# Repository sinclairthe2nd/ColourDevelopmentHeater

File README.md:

# ColourDevelopmentHeater
This is a Heating Controller Designed for Develoment of Colour film by the C-41 Process.
It uses PID,PI or P to controll A 12V heating element although other voltages are possible.
Temperature is sensed by a Pt100 and is read back to the user via a 7 Segment Display.

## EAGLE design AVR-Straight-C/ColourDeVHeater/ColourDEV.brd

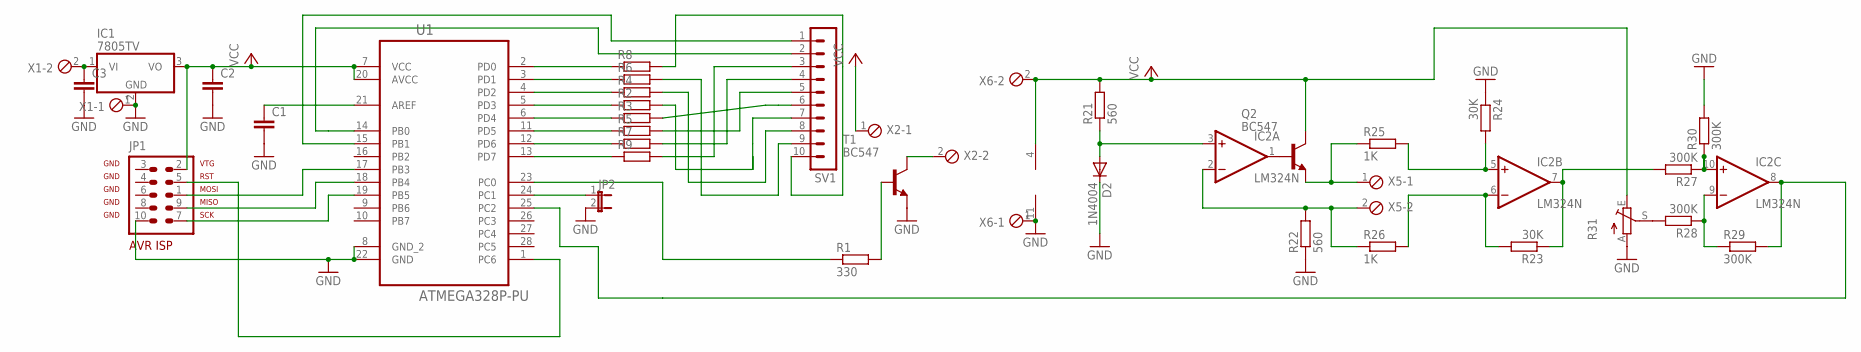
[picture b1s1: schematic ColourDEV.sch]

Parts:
C1: C-EU050-075X075; C050-075X075
C2, C3: C-EU050-025X075; C050-025X075
D2: 1N4004; DO41-10
IC1: 7805TV; TO220V
IC2: LM324N; DIL14
JP1: AVR-ISP-10
JP2: JP1E; JP1
Q2: BC547; TO92
R1: 330; M1206
R2, R3, R4, R5, R6, R7, R8, R9: R-EU_M1206; M1206
R21, R22: 560; M1206
R23, R24: 30K; M1206
R25, R26: 1K; M1206
R27, R28, R29, R30: 300K; M1206
R31: TRIM_EU-LI10; LI10
SV1: MA10-1
T1: BC547; TO92
U1: ATMEGA328P-PU; DIP254P762X457-28
X1, X2, X5, X6: MPT2; 2POL254

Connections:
GND: C1.2, C2.2, C3.2, D2.C, IC1.2 (GND), IC2.11 (V-), JP1.10, JP2.2, R22.1, R24.1, R30.2, R31.A, T1.1 (E), U1.8 (GND_2), U1.22 (GND), X1.1, X6.1
unnamed: R1.2, T1.2 (B)
unnamed: R1.1, U1.23 (PC0)
unnamed: JP1.5, U1.1 (PC6)
unnamed: JP1.1, U1.17 (PB3)
unnamed: JP1.9, U1.18 (PB4)
unnamed: JP1.7, U1.19 (PB5)
unnamed: R9.2, SV1.3
unnamed: R7.2, SV1.4
unnamed: R5.2, SV1.5
unnamed: R3.2, SV1.6
unnamed: R2.2, SV1.7
unnamed: R4.2, SV1.8
unnamed: R6.2, SV1.9
unnamed: R8.2, SV1.10
unnamed: SV1.2, U1.14 (PB0)
unnamed: SV1.1, U1.15 (PB1)
unnamed: C1.1, U1.21 (AREF)
unnamed: R5.1, U1.11 (PD5)
unnamed: R3.1, U1.6 (PD4)
unnamed: R2.1, U1.5 (PD3)
unnamed: R4.1, U1.4 (PD2)
unnamed: R6.1, U1.3 (PD1)
unnamed: R8.1, U1.2 (PD0)
unnamed: R7.1, U1.12 (PD6)
unnamed: R9.1, U1.13 (PD7)
unnamed: JP2.1, U1.24 (PC1)
unnamed: T1.3 (C), X2.2
unnamed: C3.1, IC1.1 (VI), X1.2
unnamed: D2.A, IC2.3 (+IN), R21.1
unnamed: IC2.1 (OUT), Q2.2 (B)
unnamed: Q2.1 (E), R25.1, X5.1
unnamed: IC2.2 (-IN), R22.2, R26.1, X5.2
unnamed: IC2.5 (+IN), R24.2, R25.2
unnamed: IC2.6 (-IN), R23.2, R26.2
unnamed: IC2.7 (OUT), R23.1, R27.2
unnamed: IC2.10 (+IN), R27.1, R30.1
unnamed: IC2.9 (-IN), R28.1, R29.1
unnamed: IC2.8 (OUT), R29.2, U1.25 (PC2)
unnamed: R28.2, R31.S
VCC: C2.1, IC1.3 (VO), IC2.4 (V+), JP1.2, Q2.3 (C), R21.2, R31.E, U1.7 (VCC), U1.20 (AVCC), X2.1, X6.2

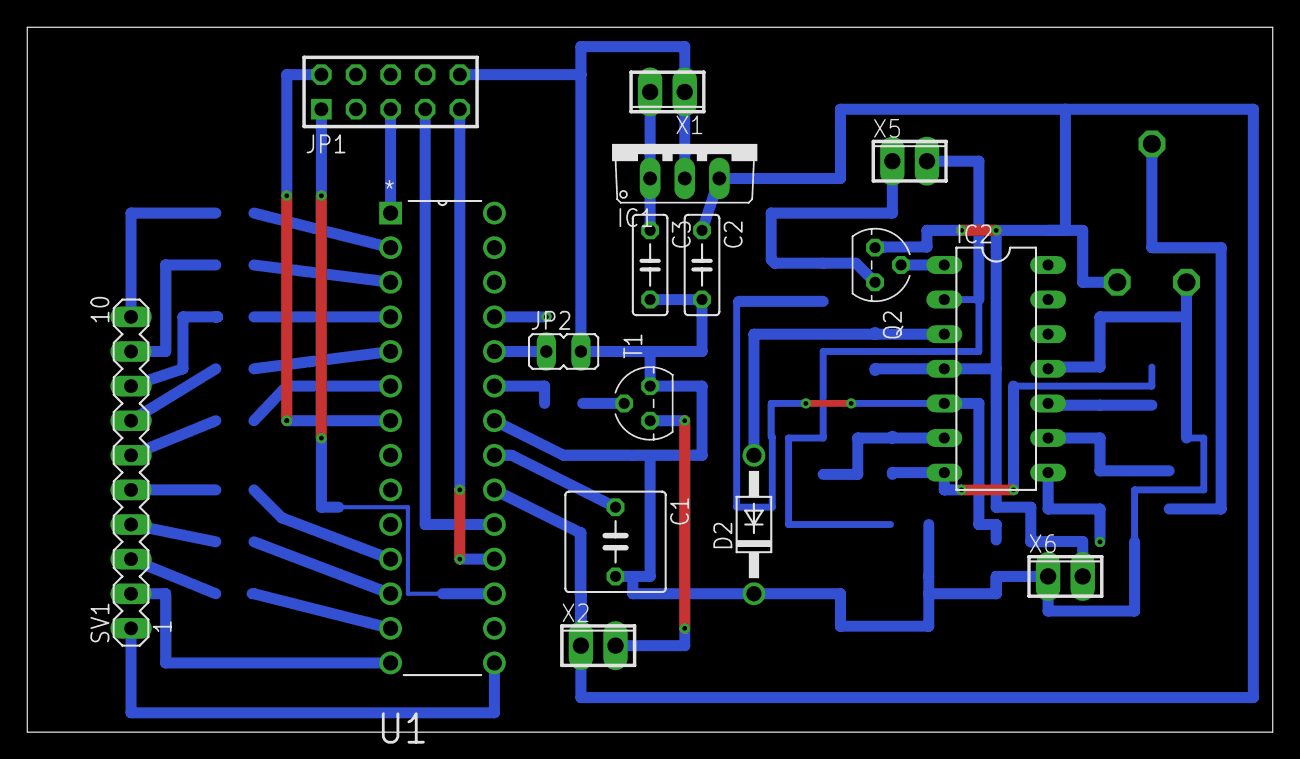
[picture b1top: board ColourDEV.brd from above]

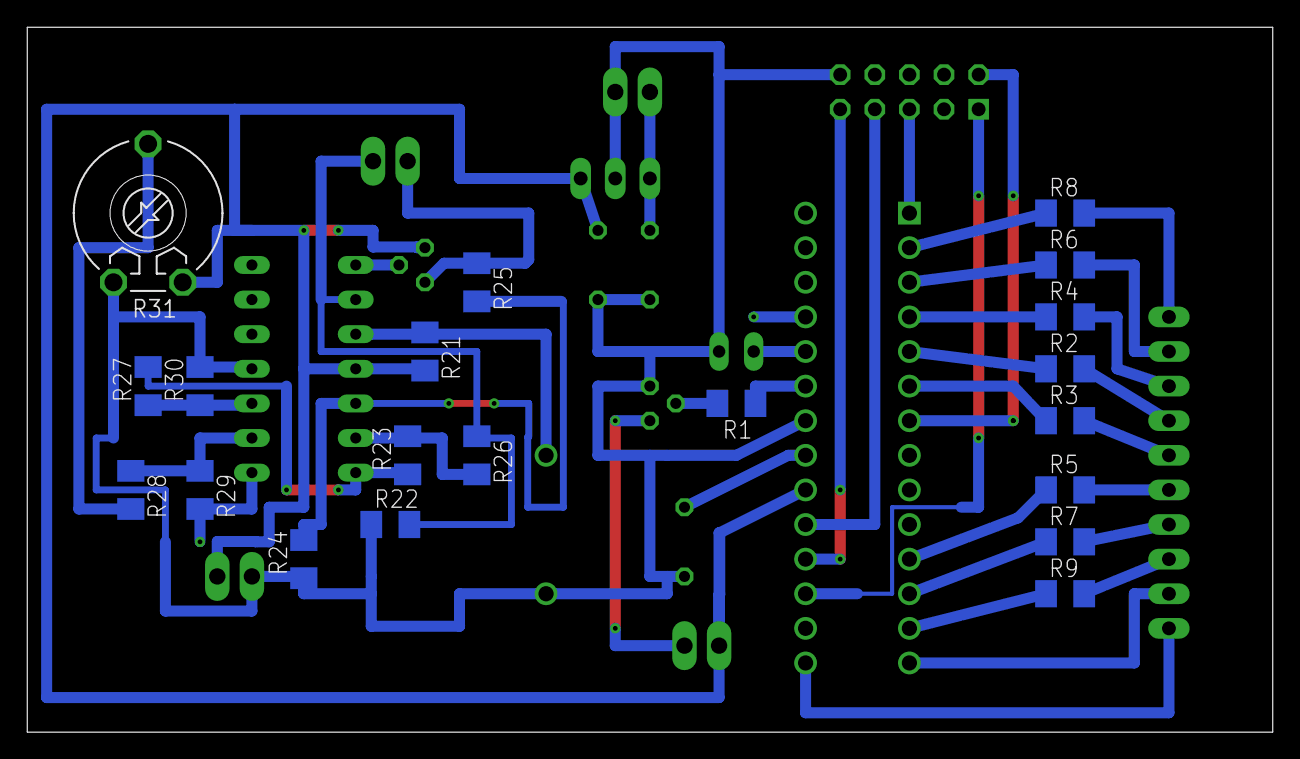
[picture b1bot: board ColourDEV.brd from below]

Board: 2 copper layers, 91.4 x 51.7 mm, 36 parts (20 on the bottom side), 41 nets.

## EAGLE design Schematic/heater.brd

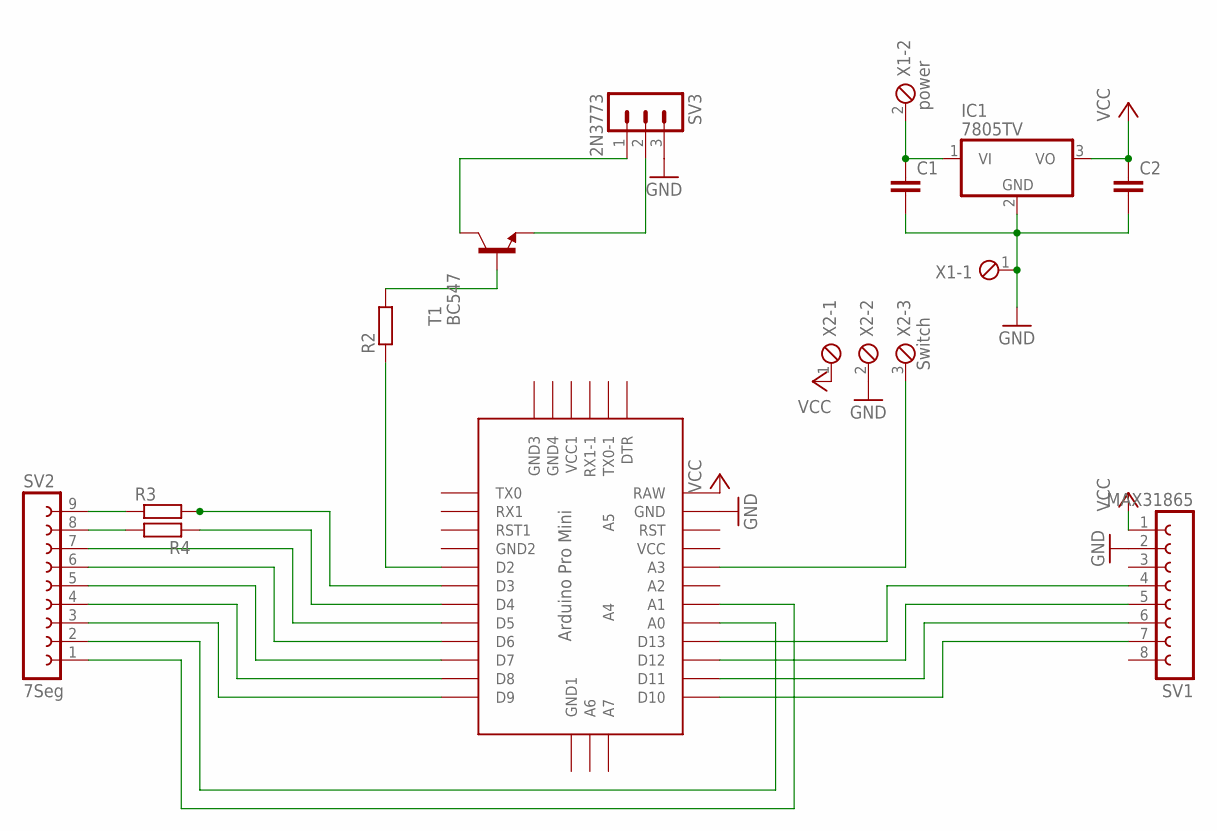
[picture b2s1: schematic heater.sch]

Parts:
C1, C2: C-EU025-050X050; C025-050X050
IC1: 7805TV; TO220V
R2, R3, R4: R-EU_0207/10; 0207/10
SV1: MAX31865; FE08
SV2: 7Seg; FE09
SV3: 2N3773; MA03-1
T1: BC547; TO92
U$1: ABK-PRO-MINI
X1: power; 2POL254
X2: Switch; 3POL254

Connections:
GND: C1.2, C2.2, IC1.2 (GND), SV1.2, SV3.3, U$1.GND, X1.1, X2.2
unnamed: C1.1, IC1.1 (VI), X1.2
unnamed: SV1.4, U$1.D13
unnamed: SV1.5, U$1.D12
unnamed: SV1.6, U$1.D11
unnamed: SV1.7, U$1.D10
unnamed: U$1.A3, X2.3
unnamed: SV3.2, T1.1 (E)
unnamed: R2.2, T1.2 (B)
unnamed: SV3.1, T1.3 (C)
unnamed: R2.1, U$1.D2
unnamed: R3.2, U$1.D3
unnamed: SV2.2, U$1.A0
unnamed: R4.2, SV2.8
unnamed: R3.1, SV2.9
unnamed: SV2.7, U$1.D5
unnamed: SV2.6, U$1.D6
unnamed: SV2.5, U$1.D7
unnamed: SV2.4, U$1.D8
unnamed: SV2.3, U$1.D9
unnamed: SV2.1, U$1.A1
unnamed: R4.1, U$1.D4
VCC: C2.1, IC1.3 (VO), SV1.1, U$1.RAW, X2.1

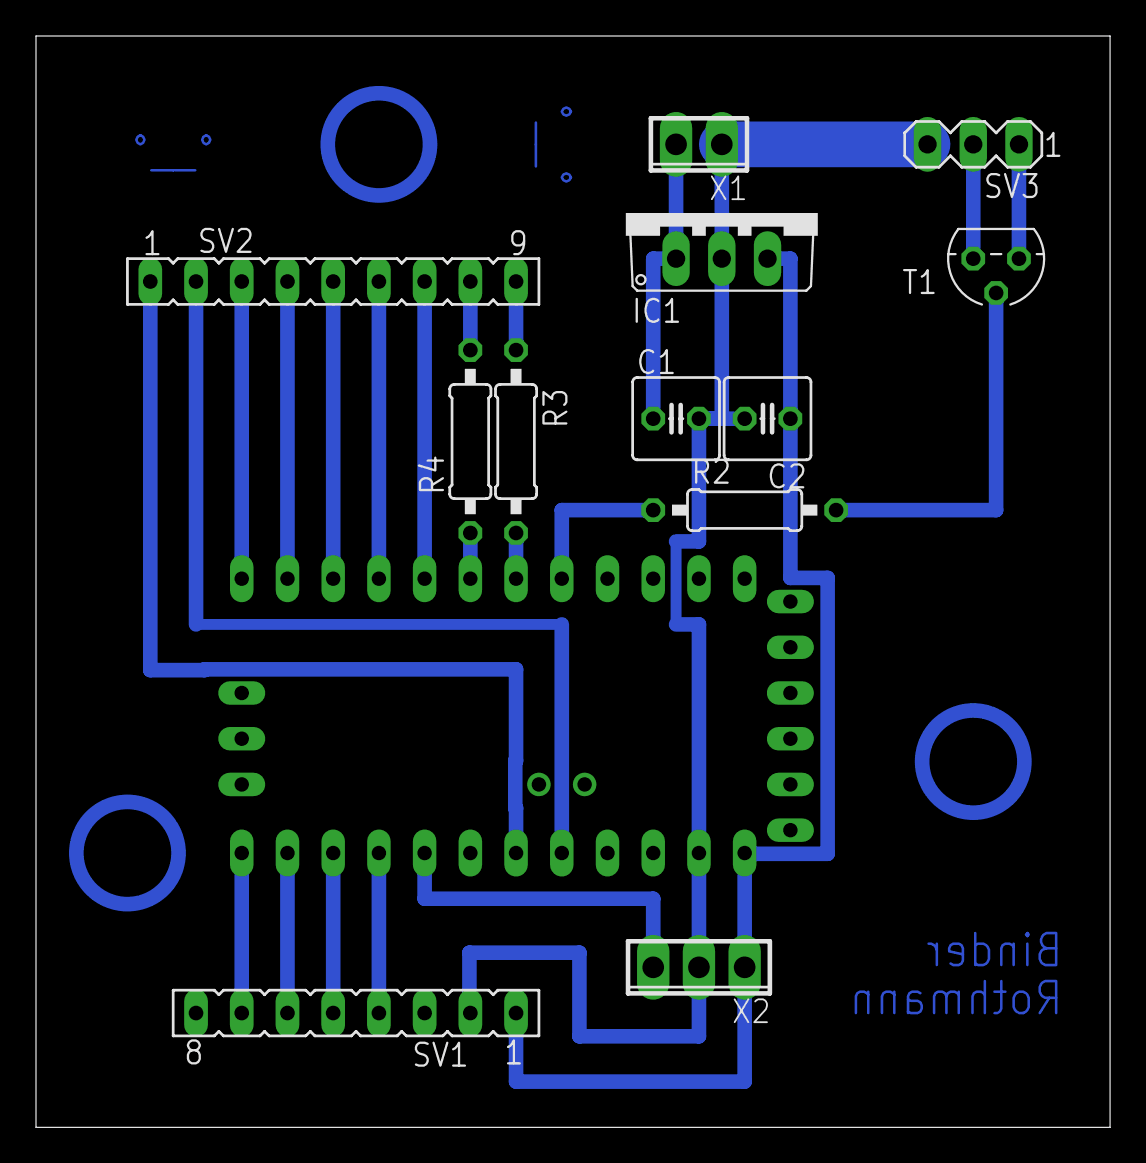
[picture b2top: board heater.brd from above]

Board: 2 copper layers, 59.7 x 60.6 mm, 13 parts (0 on the bottom side), 23 nets.

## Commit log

2018-05-28 Add Button to code; Add board and schematic
2018-08-25 This is an almost complete version that uses an analog Pt100 Frontend
2018-08-26 Added Eagle Files and Cad Files
2018-08-26 This is a Working Version of the Code
    Changed the 7-Segment Pin assignment and also made the jumper work better
2018-10-01 This adds more efficient mapping code and rearanges the code to please the mighty compiler.
2018-10-01 This adds more efficient mapping code,gets rid of an error and adds comments to the solving of the calibration equation
